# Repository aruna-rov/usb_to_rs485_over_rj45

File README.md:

# usb_to_rs485_over_rj45
usb to rs485 over rj45

## Schematic

## Pcb design

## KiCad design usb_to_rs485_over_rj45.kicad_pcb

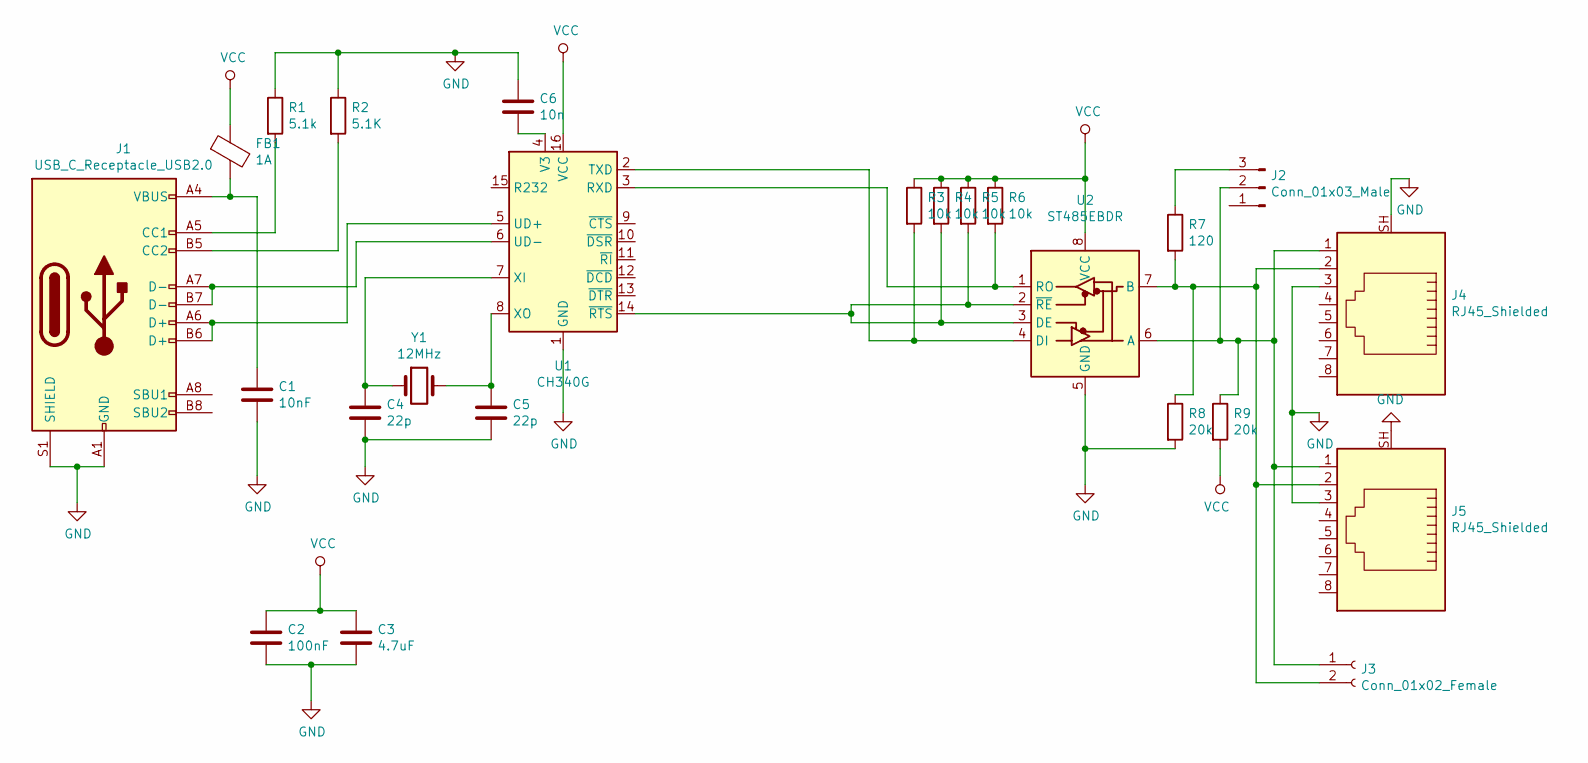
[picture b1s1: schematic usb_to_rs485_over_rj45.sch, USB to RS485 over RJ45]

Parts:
C1: 10nF; C_0603_1608Metric
C2: 100nF; C_0603_1608Metric
C3: 4.7uF; C_0603_1608Metric
C4, C5: 22p; C_0603_1608Metric
C6: 10n; C_0603_1608Metric
FB1: 1A; L_0603_1608Metric
J1: USB_C_Receptacle_USB2.0; USB_C_Receptacle_HRO_TYPE-C-31-M-12
J2: Conn_01x03_Male; PinHeader_1x03_P2.54mm_Vertical
J3: Conn_01x02_Female; PhoenixContact_MSTBVA_2,5_2-G-5,08_1x02_P5.08mm_Vertical
J4, J5: RJ45_Shielded; ASSMANN_A-2004-2-4-LPS-N-R
R1: 5.1k; R_0603_1608Metric
R2: 5.1K; R_0603_1608Metric
R3, R4, R5, R6: 10k; R_0603_1608Metric
R7: 120; R_0603_1608Metric
R8, R9: 20k; R_0603_1608Metric
U1: CH340G; SOIC-16_3.9x9.9mm_P1.27mm
U2: ST485EBDR; SOIC-8_3.9x4.9mm_P1.27mm
Y1: 12MHz; Crystal_HC49-4H_Vertical

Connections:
GND: C1.2, C2.2, C3.2, C4.2, C5.2, C6.1, J1.A1 (GND), J1.A12 (GND), J1.B1 (GND), J1.B12 (GND), J1.S1 (SHIELD), J4.3, J4.SH, J5.3, J5.SH, R1.1, R2.1, R8.2, U1.1 (GND), U2.5 (GND)
unnamed: C1.1, FB1.2, J1.A4 (VBUS), J1.A9 (VBUS), J1.B4 (VBUS), J1.B9 (VBUS)
unnamed: C4.1, U1.7 (XI), Y1.1
unnamed: C5.1, U1.8 (XO), Y1.2
unnamed: C6.2, U1.4 (V3)
unnamed: J1.A5 (CC1), R1.2
unnamed: J1.A6 (D+), J1.B6 (D+), U1.5 (UD+)
unnamed: J1.A7 (D-), J1.B7 (D-), U1.6 (UD-)
unnamed: J1.B5 (CC2), R2.2
unnamed: J2.2, J3.1, J4.1, J5.1, R9.1, U2.6 (A)
unnamed: J2.3, R7.1
unnamed: J3.2, J4.2, J5.2, R7.2, R8.1, U2.7 (B)
unnamed: R3.2, U1.2 (TXD), U2.4 (DI)
unnamed: R4.2, R5.2, U1.14 (~RTS), U2.2 (~RE), U2.3 (DE)
unnamed: R6.2, U1.3 (RXD), U2.1 (RO)
VCC: C2.1, C3.1, FB1.1, R3.1, R4.1, R5.1, R6.1, R9.2, U1.16 (VCC), U2.8 (VCC)

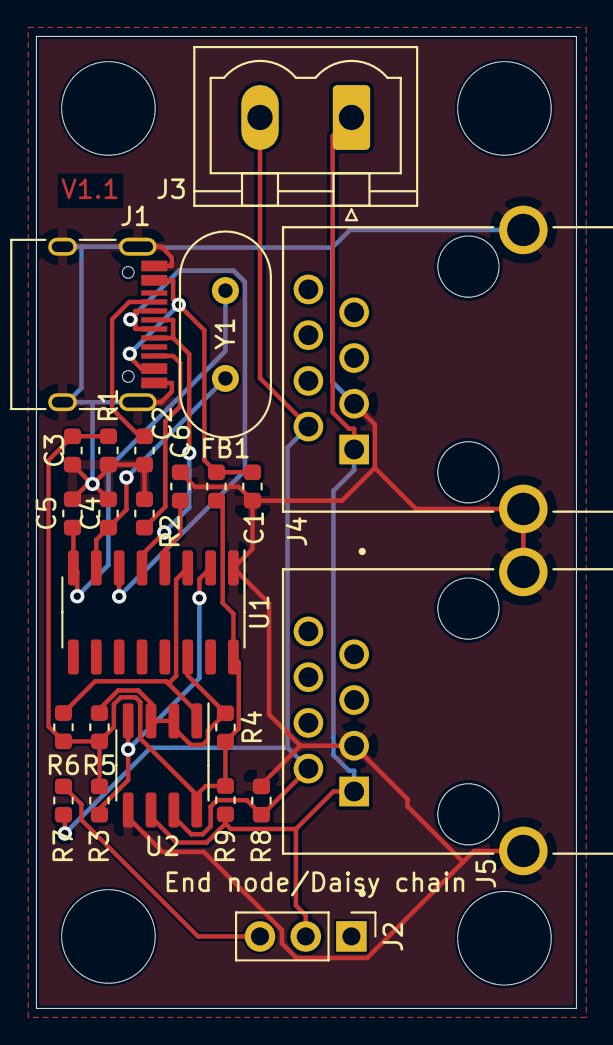
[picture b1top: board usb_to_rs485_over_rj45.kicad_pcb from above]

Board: 2 copper layers, 30.0 x 54.0 mm, 24 parts (0 on the bottom side), 16 nets.

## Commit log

2020-02-28 usb to rs485 over rj45 init
2020-02-28 v1.1 documentation
2020-08-28 GNU GPLv3 license
